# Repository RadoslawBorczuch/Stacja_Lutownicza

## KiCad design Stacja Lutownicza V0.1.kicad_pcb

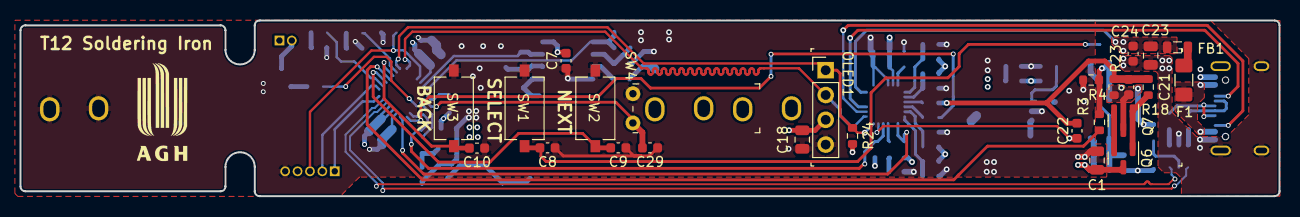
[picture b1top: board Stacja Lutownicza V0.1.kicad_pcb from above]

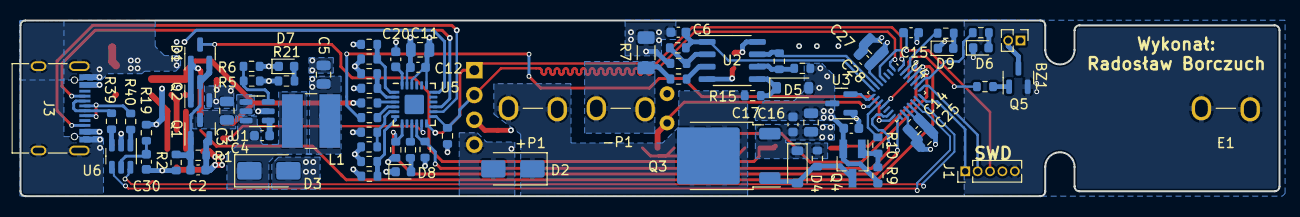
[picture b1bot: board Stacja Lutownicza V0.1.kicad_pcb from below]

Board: 4 copper layers, 129.0 x 18.0 mm, 104 parts (79 on the bottom side), 66 nets.

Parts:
+P1: 520 Fuse Clip
-P1: 520 Fuse Clip
BZ1: Buzzer; PinHeader_1x02_P1.27mm_Vertical
C1, C3, C16, C23: 22u; C_0805_2012Metric
C2, C4, C6, C7, C8, C9, C10, C12, C14, C15, C17, C24, C28, C29, C30, C31: 100n; C_0603_1608Metric
C5, C11, C18, C25, C27: 10u; C_0805_2012Metric
C20, C21, C22: 1u; C_0603_1608Metric
D1: BAT54C; SOT-23
D2, D3: SS34; D_SMA
D4: 11V; D_SOD-123
D5: 3V3; D_SOD-123
D6: BLUE; LED_0603_1608Metric
D7, D8: RED; LED_0603_1608Metric
D9: GREEN; LED_0603_1608Metric
E1: 520 Fuse Clip
F1: 3.5A; Fuse_1206_3216Metric_Pad1.42x1.75mm_HandSolder
FB1: 100 @ 100MHz; L_0805_2012Metric
J1: Conn_01x05; PinHeader_1x05_P1.27mm_Vertical
J3: USB_C_Receptacle_USB2.0; USB_C_Receptacle_XKB_U262-16XN-4BVC11
L1: 22u; L_TracoPower_TCK-047_5.2x5.8mm
OLED1: Oled module 128x32
Q1, Q6, Q7: AO3401A; SOT-23
Q2: AO3400A; SOT-23
Q3: SUD09P10; TO-252-2
Q4: MMBT3904; SOT-23_Handsoldering
Q5: MMBT3904; SOT-23
R1: 430k; R_0603_1608Metric
R2, R8: 270k; R_0603_1608Metric
R3, R10, R14: 100R; R_0603_1608Metric
R4: 47k; R_0603_1608Metric
R5: 68k; R_0603_1608Metric
R6: 22k; R_0603_1608Metric
R7: 0R1 1W; R_1206_3216Metric_Pad1.30x1.75mm_HandSolder
R9, R11, R16, R20, R21, R38: 1k; R_0603_1608Metric
R12, R13, R15, R19, R23: 10k; R_0603_1608Metric
R17: 200k; R_0603_1608Metric
R18, R22, R24, R25, R26, R27, R28, R29, R30, R31, R32, R33, R34, R35, R36, R37: 2k2; R_0603_1608Metric
R39, R40: 22R; R_0603_1608Metric
SW1, SW2, SW3: SW_Push; SW_Tactile_SPST_NO_Straight_CK_PTS636Sx25SMTRLFS
SW4: SW_Reed; Tilt_Switch
U1: AP64060Q; TSOT-23-6
U2: TSZ182; SO-8_3.9x4.9mm_P1.27mm
U3: MCP9700Ax-ETT; SOT-23
U4: STM32F042G4Ux; QFN-28_4x4mm_P0.5mm
U5: CYPD3177; InvenSense_QFN-24_4x4mm_P0.5mm_NoMask
U6: USBLC6-2SC6; SOT-23-6

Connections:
+3V3: BZ1.1 (-), C5.1, C7.2, C11.1, C12.1, C14.1, C18.1, C25.1, C27.1, C28.1, C31.2, J1.4, L1.2, OLED1.3 (VCC), R5.1, R21.1, R24.1, R25.1, R27.1, R28.1, R30.1, R32.1, R34.1, R37.1, U2.8 (V+), U3.1 (V_{DD}), U4.5 (VDDA), U4.17 (VDD), U4.18 (VDDIO2), U5.23 (VDDD)
Buzzer: R14.1, U4.11 (PA5)
CC1: J3.A5 (CC1), U5.15 (CC1)
CC2: J3.B5 (CC2), U5.14 (CC2)
FLIP: R37.2, U4.13 (PA7), U5.10 (FLIP)
GND: C1.2, C3.2, C5.2, C6.1, C7.1, C8.1, C9.1, C10.1, C11.2, C12.2, C14.2, C15.2, C16.2, C17.2, C18.2, C20.2, C23.2, C24.2, C25.2, C27.2, C28.2, C29.1, C30.1, C31.1, D2.2 (A), D3.2 (A), D5.2 (A), D6.1 (K), D7.1 (K), D8.1 (K), D9.1 (K), E1.1, J1.5, J3.A1 (GND), J3.A12 (GND), J3.B1 (GND), J3.B12 (GND), J3.S1 (SHIELD), OLED1.4 (GND), Q2.2 (S), Q4.2 (E), Q5.2 (E), R2.2, R4.2, R6.2, R7.1, R9.2, R11.2, R16.2, R29.2, R31.2, R33.2, R35.2, SW1.1, SW2.1, SW3.1, SW4.1, U1.2 (GND), U2.4 (V-), U3.3 (GND), U4.16 (VSSA), U5.19 (GND), U5.22 (GND), U6.2 (GND)
INT: R27.2, U4.15 (PB1), U5.7 (HPI_INT)
NRST: C15.1, J1.3, U4.4 (NRST)
unnamed: BZ1.2 (+), Q5.3 (C)
unnamed: C21.2, C22.2, R18.2, R22.1, R23.1
unnamed: C4.1, D3.1 (K), L1.1, U1.6 (SW)
unnamed: D4.2 (A), Q3.1 (G), Q4.3 (C), R8.2
unnamed: D5.1 (K), R15.2, U2.5 (+)
unnamed: D6.2 (A), R20.2
unnamed: D7.2 (A), R21.2
unnamed: D8.2 (A), R26.2
unnamed: D9.2 (A), R38.2
unnamed: F1.1, FB1.2
unnamed: F1.2, J3.A4 (VBUS), J3.A9 (VBUS), J3.B4 (VBUS), J3.B9 (VBUS)
unnamed: J3.A6 (D+), J3.B6 (D+), R40.2
unnamed: J3.A7 (D-), J3.B7 (D-), R39.2
unnamed: C2.2, D1.2, Q1.1 (G), Q2.3 (D), R1.2, R2.1
unnamed: D1.1, Q2.1 (G), R3.1, R4.1
unnamed: Q4.1 (B), R9.1, R10.2
unnamed: Q5.1 (B), R14.2
unnamed: Q6.1 (G), Q7.1 (G), R18.1
unnamed: Q6.2 (S), Q7.2 (S)
unnamed: C4.2, U1.1 (BST)
unnamed: R5.2, R6.1, U1.3 (FB)
unnamed: R13.2, U2.3 (+)
unnamed: R11.1, R12.1, U2.2 (-)
unnamed: R16.1, R17.1, U2.6 (-)
unnamed: R26.1, U5.9 (FAULT)
unnamed: R32.2, R33.1, U5.5 (ISNK_COARSE)
unnamed: R34.2, R35.1, U5.6 (ISNK_FINE)
unnamed: R36.2, U5.4 (SAFE_PWR_EN)
unnamed: R22.2, U5.3 (VBUS_FET_EN)
unnamed: R28.2, R29.1, U5.2 (VBUS_MAX)
unnamed: R30.2, R31.1, U5.1 (VBUS_MIN)
unnamed: C20.1, U5.24 (VCCD)
unnamed: C30.2, R19.1, U6.5 (VBUS)
PD_SAFE: R36.1, U4.14 (PB0)
PS_LED: R38.1, U4.27 (PB6)
SCL: OLED1.2 (SCL), R25.2, U4.1 (PB8), U5.13 (HPI_SCL)
SDA: OLED1.1 (SDA), R24.2, U4.28 (PB7), U5.12 (HPI_SDA)
SWCLK: J1.2, U4.22 (PA14)
SWDIO: J1.1, U4.21 (PA13)
SW_BACK: C10.2, SW3.2, U4.26 (PB5)
SW_NEXT: C9.2, SW2.2, U4.24 (PB3)
SW_ON/OFF: C8.2, D1.3, SW1.2
SW_SELECT: R3.2, U4.25 (PB4)
T12_Current: C6.2, R12.2, U2.1, U4.7 (PA1)
T12_PWM: R10.1, U4.10 (PA4)
T12_Thermocouple: R17.2, U2.7, U4.6 (PA0)
T12_V+: +P1.1, D2.1 (K), Q3.2 (D), R15.1
T12_V-: -P1.1, R7.2, R13.1
TEMP_AMBIENT: U3.2 (V_{OUT}), U4.8 (PA2)
TILT_SW: C29.2, SW4.2, U4.9 (PA3)
USB_CONN_D+: R40.1, U6.1 (I/O1)
USB_CONN_D-: R39.1, U6.3 (I/O2)
USB_D+: U4.20 (PA10/PA12), U6.6 (I/O1)
USB_D-: U4.19 (PA9/PA11), U6.4 (I/O2)
U_LED: R20.1, U4.23 (PA15)
VBUS: C21.1, C23.1, C24.1, FB1.1, Q7.3 (D), R19.2, R23.2, U5.18 (VBUS_IN)
VCCQ: C3.1, Q1.3 (D), U1.4 (EN), U1.5 (VIN)
VDC: C1.1, C2.1, C16.1, C17.1, C22.1, D4.1 (K), Q1.2 (S), Q3.3 (S), Q6.3 (D), R1.1, R8.1, U5.11 (VDC_OUT)
